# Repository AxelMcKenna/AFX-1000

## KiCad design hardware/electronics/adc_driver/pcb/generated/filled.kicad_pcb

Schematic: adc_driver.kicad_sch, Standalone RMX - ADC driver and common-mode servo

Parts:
C1, C2, C15, C16: 1pF C0G +/-0.1pF; C_0805_2012Metric
C3, C17: 47pF C0G 5%; C_0805_2012Metric
C4, C5, C18, C19: 22pF C0G 5%; C_0805_2012Metric
C6, C20: 100nF 25V X7R; C_0805_2012Metric
C7, C21: 1uF 63V film 10%; C_Rect_L7.2mm_W5.0mm_P5.00mm
C8, C22: 10uF 16V X7R; C_1206_3216Metric
C9, C23: 47uF 16V X7R; C_1210_3225Metric
C10, C11, C24, C25: 47uF 6.3V X7R; C_1206_3216Metric
C12, C26: 2.2uF 16V X7R; C_0805_2012Metric
C13, C14, C27, C28: 100nF 16V X7R; C_0805_2012Metric
C29, C30, C31, C32: 100nF 50V X7R; C_0805_2012Metric
C33, C34: 10uF 50V X7R; C_1210_3225Metric
D1, D2: BAT54S,215; SOT-23
J1: Conn_01x03; PinHeader_1x03_P2.54mm_Vertical
J2: Conn_01x07; PinHeader_1x07_P2.54mm_Vertical
J3, J4: Conn_01x04; PinHeader_1x04_P2.54mm_Vertical
R1, R2, R17, R18: 2.49k 0.1%; R_0805_2012Metric
R3, R4, R19, R20: 1.21k 0.1%; R_0805_2012Metric
R5, R6, R21, R22: 3.32R 0.1%; R_0805_2012Metric
R7, R23: 1M 1%; R_0805_2012Metric
R8, R9, R24, R25: 1M 0.1%; R_0805_2012Metric
R10, R11, R26, R27: 100k 0.1%; R_0805_2012Metric
R12, R28: 100M 1%; R_0805_2012Metric
R13, R29: 10k 1%; R_0805_2012Metric
R14, R30: 4.7k 1%; R_0805_2012Metric
R15, R31: 100k 1%; R_0805_2012Metric
R16, R32: 1R 1%; R_0805_2012Metric
R33: 1k 1%; R_0805_2012Metric
U1, U2: THS4551IDGKR; VSSOP-8_3x3mm_P0.65mm
U3: OPA1656ID; SOIC-8_3.9x4.9mm_P1.27mm
U4: OPA4192ID; SOIC-14_3.9x8.7mm_P1.27mm
U5, U6: LM7705MM/NOPB; VSSOP-8_3x3mm_P0.65mm

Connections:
/ADC_LN: C3.2, C5.1, J2.2, R3.1, R6.2, R11.1
/ADC_LP: C3.1, C4.1, J2.1, R4.1, R5.2, R10.1
/ADC_RN: C17.2, C19.1, J2.5, R19.1, R22.2, R27.1
/ADC_RP: C17.1, C18.1, J2.4, R20.1, R21.2, R26.1
/AGND: C4.2, C5.2, C6.2, C9.2, C10.2, C11.2, C12.2, C13.2, C14.2, C18.2, C19.2, C20.2, C23.2, C24.2, C25.2, C26.2, C27.2, C28.2, C29.2, C30.2, C31.2, C32.2, C33.2, C34.2, D1.1 (A1), D2.1 (A1), J1.2, J2.3, J3.2, J4.1, R2.1, R7.2, R9.2, R15.2, R18.1, R23.2, R25.2, R31.2, R33.2, U5.2 (VSS_A), U5.3 (SD), U5.5 (VSS_B), U6.2 (VSS_A), U6.3 (SD), U6.5 (VSS_B)
/BUF_L: R1.1, U3.1 (A_OUT), U3.2 (A-)
/BUF_R: R17.1, U3.6 (B-), U3.7 (B_OUT)
/CM_DRIVE_L: C7.1, R12.1, R13.1, U4.7 (B_OUT)
/CM_DRIVE_R: C21.1, R28.1, R29.1, U4.14 (D_OUT)
/CM_SENSE_L: C7.2, R10.2, R11.2, R12.2, U4.6 (B-)
/CM_SENSE_R: C21.2, R26.2, R27.2, R28.2, U4.13 (D-)
/DRV_ENABLE: J4.2, R14.1, R30.1
/DRV_LN: C1.1, R6.1, U1.5 (OUT-)
/DRV_LP: C2.1, R5.1, U1.4 (OUT+)
/DRV_RN: C15.1, R22.1, U2.5 (OUT-)
/DRV_RP: C16.1, R21.1, U2.4 (OUT+)
/FB_N_L: C2.2, R2.2, R4.2, U1.1 (IN-)
/FB_N_R: C16.2, R18.2, R20.2, U2.1 (IN-)
/FB_P_L: C1.2, R1.2, R3.2, U1.8 (IN+)
/FB_P_R: C15.2, R17.2, R19.2, U2.8 (IN+)
/FLY_N_L: C8.2, U5.8 (CF-)
/FLY_N_R: C22.2, U6.8 (CF-)
/FLY_P_L: C8.1, U5.1 (CF+)
/FLY_P_R: C22.1, U6.1 (CF+)
/N12: C30.1, C32.1, C34.1, J3.3, U3.4 (V-), U4.11 (V-)
/NBIAS_L: C11.1, C14.1, J4.3, R16.2, U1.6 (VS-)
/NBIAS_R: C25.1, C28.1, J4.4, R32.2, U2.6 (VS-)
/NPUMP_L: C10.1, R16.1, U5.6 (VOUT)
/NPUMP_R: C24.1, R32.1, U6.6 (VOUT)
/P12: C29.1, C31.1, C33.1, J3.1, U3.8 (V+), U4.4 (V+)
/PD_L: R14.2, R15.1, U1.7 (PD)
/PD_R: R30.2, R31.1, U2.7 (PD)
/PRE_OUT_L: J1.1, R7.1, U3.3 (A+)
/PRE_OUT_R: J1.3, R23.1, U3.5 (B+)
/REF_ADC1: J2.6, R8.1
/REF_ADC2: J2.7, R24.1
/REF_DIV_L: C6.1, R8.2, R9.1, U4.3 (A+)
/REF_DIV_R: C20.1, R24.2, R25.1, U4.10 (C+)
/REF_HALF_L: U4.1 (A_OUT), U4.2 (A-), U4.5 (B+)
/REF_HALF_R: U4.8 (C_OUT), U4.9 (C-), U4.12 (D+)
/RES_L: C9.1, U5.7 (CRES)
/RES_R: C23.1, U6.7 (CRES)
/V5_REG: C12.1, C13.1, C26.1, C27.1, D1.2 (K2), D2.2 (K2), J3.4, R33.1, U1.3 (VS+), U2.3 (VS+), U5.4 (VDD), U6.4 (VDD)
/VOCM_L: D1.3 (K1_A2), R13.2, U1.2 (VOCM)
/VOCM_R: D2.3 (K1_A2), R29.2, U2.2 (VOCM)

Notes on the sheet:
E12 ADC driver prototype: remote raw-pin gain feedback, separate reference-half servos, low-voltage output rails.
No PCB or bench validation. Actual converter loading, stability, full scale/noise, bias-rail windows and power faults require qualification.
THS4551 +/-outputs use V5_REG and per-channel LM7705 negative bias; no direct +/-12V output rail on raw ADC drivers.
Future PRE_ANALOG_OK must include V5_REG and BOTH filtered negative-bias windows. E09 CHIP_EN drives DRV_ENABLE.
U3 preserves E10 high input impedance. U4 buffers references/2 and slowly controls ADC-pin average; no unbuffered shared reference load.

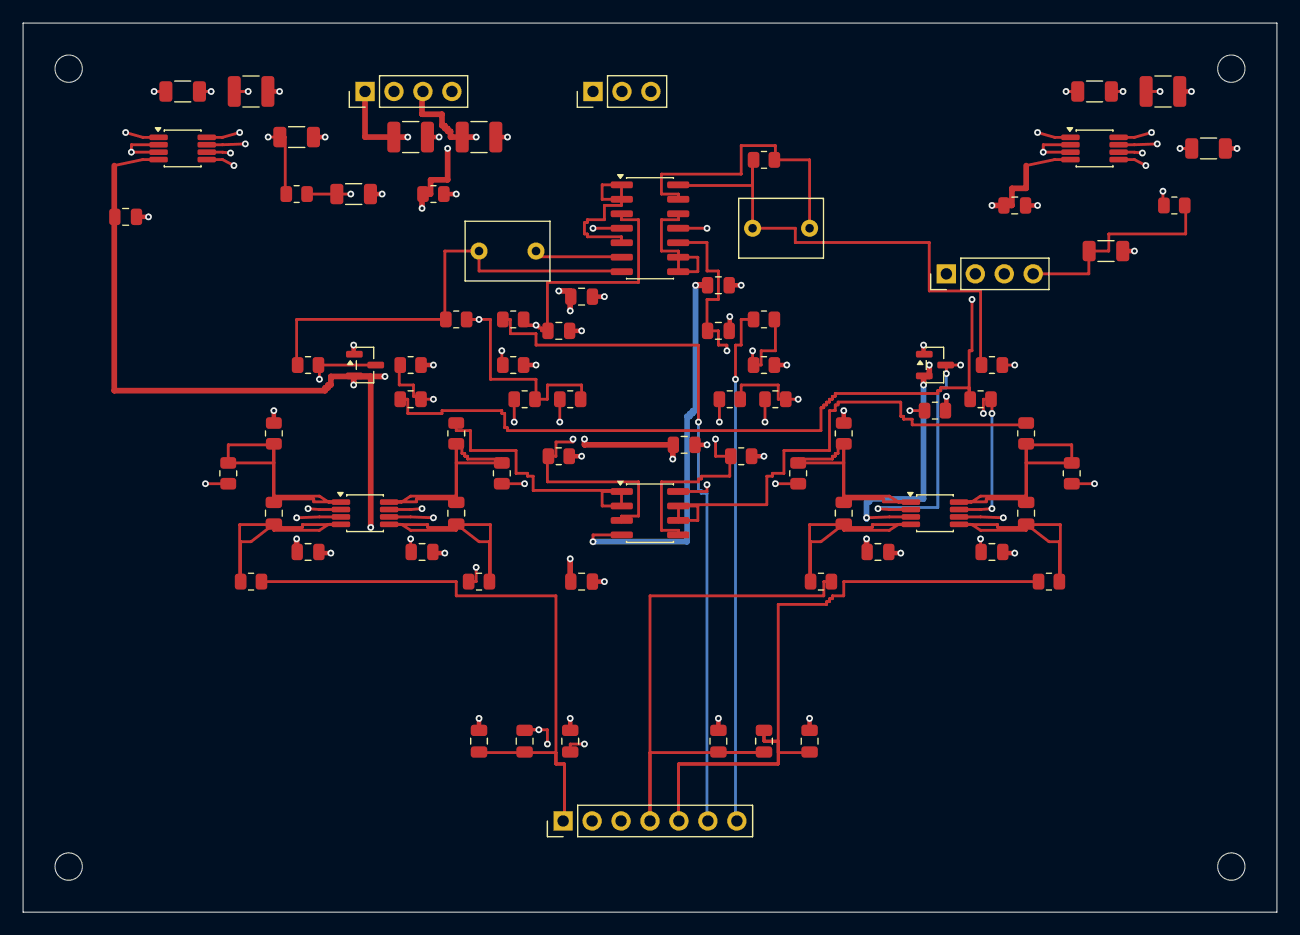
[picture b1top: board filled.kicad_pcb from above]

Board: 6 copper layers, 110.0 x 78.0 mm, 83 parts (0 on the bottom side), 45 nets.

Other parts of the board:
H1, H2, H3, H4: M2_CLEARANCE; M2_Clearance

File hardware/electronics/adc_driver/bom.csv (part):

Reference,Part_or_value,Footprint_candidate,Datasheet,Design_note
U1,THS4551IDGKR,Package_SO:VSSOP-8_3x3mm_P0.65mm,https://www.ti.com/lit/ds/symlink/ths4551.pdf,Remote raw-pin resistive feedback; local1pF high-frequency feedback. Low-voltage rails only.
U2,THS4551IDGKR,Package_SO:VSSOP-8_3x3mm_P0.65mm,https://www.ti.com/lit/ds/symlink/ths4551.pdf,Remote raw-pin resistive feedback; local1pF high-frequency feedback. Low-voltage rails only.
U3,OPA1656ID,Package_SO:SOIC-8_3.9x4.9mm_P1.27mm,https://www.ti.com/lit/ds/symlink/opa1656.pdf,High-impedance unity buffers preserve E10 load >=100k;1M returns per channel.
U4,OPA4192ID,Package_SO:SOIC-14_3.9x8.7mm_P1.27mm,https://www.ti.com/lit/ds/symlink/opa4192.pdf,A/C buffer separate reference halves;B/D slow average raw ADC pins to reference/2. No shared channel reference.
U5,LM7705MM/NOPB,Package_SO:VSSOP-8_3x3mm_P0.65mm,https://www.ti.com/lit/ds/symlink/lm7705.pdf,One bias generator/channel; output-current allocation <=20mA; effective pump capacitors must meet datasheet test values.
U6,LM7705MM/NOPB,Package_SO:VSSOP-8_3x3mm_P0.65mm,https://www.ti.com/lit/ds/symlink/lm7705.pdf,One bias generator/channel; output-current allocation <=20mA; effective pump capacitors must meet datasheet test values.
R1,2.49k 0.1%,Resistor_SMD:R_0805_2012Metric,,FDA source resistor; source buffer directly drives this resistive load
R2,2.49k 0.1%,Resistor_SMD:R_0805_2012Metric,,Matched ground leg
R3,1.21k 0.1%,Resistor_SMD:R_0805_2012Metric,,Remote negative-output feedback; gain reserves ADC clipping margin
R4,1.21k 0.1%,Resistor_SMD:R_0805_2012Metric,,Remote positive-output feedback
R5,3.32R 0.1%,Resistor_SMD:R_0805_2012Metric,,Raw-pin isolation; inside low-frequency feedback
R6,3.32R 0.1%,Resistor_SMD:R_0805_2012Metric,,Raw-pin isolation; inside low-frequency feedback
R7,1M 1%,Resistor_SMD:R_0805_2012Metric,,E10 load1M plus FET input; no direct low-resistance FDA load
R8,1M 0.1%,Resistor_SMD:R_0805_2012Metric,,High-impedance reference divider; load about1.65uA/channel
R9,1M 0.1%,Resistor_SMD:R_0805_2012Metric,,Reference half; hot input bias/offset allocation included in analysis
R10,100k 0.1%,Resistor_SMD:R_0805_2012Metric,,Common-mode average sense
R11,100k 0.1%,Resistor_SMD:R_0805_2012Metric,,Common-mode average sense
R12,100M 1%,Resistor_SMD:R_0805_2012Metric,,Finite dc servo gain; clean board/leakage qualification required
R13,10k 1%,Resistor_SMD:R_0805_2012Metric,,VOCM clamp current limit
R14,4.7k 1%,Resistor_SMD:R_0805_2012Metric,,3.3V CHIP_EN from E09; missing enable defaults off
R15,100k 1%,Resistor_SMD:R_0805_2012Metric,,PD pull-down
R16,1R 1%,Resistor_SMD:R_0805_2012Metric,,Bias-rail ripple filter; signed load drop included in headroom screen
C1,1pF C0G +/-0.1pF,Capacitor_SMD:C_0805_2012Metric,,Local high-frequency feedback; PCB parasitics and actual FDA loop need verification
C2,1pF C0G +/-0.1pF,Capacitor_SMD:C_0805_2012Metric,,Local high-frequency feedback
C3,47pF C0G 5%,Capacitor_SMD:C_0805_2012Metric,,"Differential RF capacitor, not a proven switched-capacitor kickback model"
C4,22pF C0G 5%,Capacitor_SMD:C_0805_2012Metric,,Raw-pin RF common-mode cap
C5,22pF C0G 5%,Capacitor_SMD:C_0805_2012Metric,,Raw-pin RF common-mode cap
C6,100nF 25V X7R,Capacitor_SMD:C_0805_2012Metric,,Effective50..150nF allocation; reference-half filter
C7,1uF 63V film 10%,Capacitor_THT:C_Rect_L7.2mm_W5.0mm_P5.00mm,,"WIMA MKS2C041001F00KSSD; servo effective0.9..1.1uF, leakage qualification required"
C8,10uF 16V X7R,Capacitor_SMD:C_1206_3216Metric,,Require effective >=5uF at actual flying-cap bias
C9,47uF 16V X7R,Capacitor_SMD:C_1210_3225Metric,,Require effective >=22uF at about5V negative reserve bias
C10,47uF 6.3V X7R,Capacitor_SMD:C_1206_3216Metric,,Require effective >=22uF; native LM7705 output capacitor
C11,47uF 6.3V X7R,Capacitor_SMD:C_1206_3216Metric,,Require effective >=22uF; post1Ohm bias filter
C12,2.2uF 16V X7R,Capacitor_SMD:C_0805_2012Metric,,Local pump input; require effective >=1uF
C13,100nF 16V X7R,Capacitor_SMD:C_0805_2012Metric,,Local FDA positive bypass
C14,100nF 16V X7R,Capacitor_SMD:C_0805_2012Metric,,Local FDA negative bypass
D1,"BAT54S,215",Package_TO_SOT_SMD:SOT-23,https://assets.nexperia.com/documents/data-sheet/BAT54S.pdf,Series Schottky pair clamps VOCM; not a raw ADC signal shunt.
R17,2.49k 0.1%,Resistor_SMD:R_0805_2012Metric,,FDA source resistor; source buffer directly drives this resistive load
R18,2.49k 0.1%,Resistor_SMD:R_0805_2012Metric,,Matched ground leg
R19,1.21k 0.1%,Resistor_SMD:R_0805_2012Metric,,Remote negative-output feedback; gain reserves ADC clipping margin
R20,1.21k 0.1%,Resistor_SMD:R_0805_2012Metric,,Remote positive-output feedback
R21,3.32R 0.1%,Resistor_SMD:R_0805_2012Metric,,Raw-pin isolation; inside low-frequency feedback
R22,3.32R 0.1%,Resistor_SMD:R_0805_2012Metric,,Raw-pin isolation; inside low-frequency feedback
R23,1M 1%,Resistor_SMD:R_0805_2012Metric,,E10 load1M plus FET input; no direct low-resistance FDA load
R24,1M 0.1%,Resistor_SMD:R_0805_2012Metric,,High-impedance reference divider; load about1.65uA/channel
R25,1M 0.1%,Resistor_SMD:R_0805_2012Metric,,Reference half; hot input bias/offset allocation included in analysis
R26,100k 0.1%,Resistor_SMD:R_0805_2012Metric,,Common-mode average sense
R27,100k 0.1%,Resistor_SMD:R_0805_2012Metric,,Common-mode average sense
R28,100M 1%,Resistor_SMD:R_0805_2012Metric,,Finite dc servo gain; clean board/leakage qualification required
R29,10k 1%,Resistor_SMD:R_0805_2012Metric,,VOCM clamp current limit
R30,4.7k 1%,Resistor_SMD:R_0805_2012Metric,,3.3V CHIP_EN from E09; missing enable defaults off
R31,100k 1%,Resistor_SMD:R_0805_2012Metric,,PD pull-down
R32,1R 1%,Resistor_SMD:R_0805_2012Metric,,Bias-rail ripple filter; signed load drop included in headroom screen
C15,1pF C0G +/-0.1pF,Capacitor_SMD:C_0805_2012Metric,,Local high-frequency feedback; PCB parasitics and actual FDA loop need verification
C16,1pF C0G +/-0.1pF,Capacitor_SMD:C_0805_2012Metric,,Local high-frequency feedback
C17,47pF C0G 5%,Capacitor_SMD:C_0805_2012Metric,,"Differential RF capacitor, not a proven switched-capacitor kickback model"
C18,22pF C0G 5%,Capacitor_SMD:C_0805_2012Metric,,Raw-pin RF common-mode cap
C19,22pF C0G 5%,Capacitor_SMD:C_0805_2012Metric,,Raw-pin RF common-mode cap
C20,100nF 25V X7R,Capacitor_SMD:C_0805_2012Metric,,Effective50..150nF allocation; reference-half filter
C21,1uF 63V film 10%,Capacitor_THT:C_Rect_L7.2mm_W5.0mm_P5.00mm,,"WIMA MKS2C041001F00KSSD; servo effective0.9..1.1uF, leakage qualification required"
C22,10uF 16V X7R,Capacitor_SMD:C_1206_3216Metric,,Require effective >=5uF at actual flying-cap bias
C23,47uF 16V X7R,Capacitor_SMD:C_1210_3225Metric,,Require effective >=22uF at about5V negative reserve bias
C24,47uF 6.3V X7R,Capacitor_SMD:C_1206_3216Metric,,Require effective >=22uF; native LM7705 output capacitor
C25,47uF 6.3V X7R,Capacitor_SMD:C_1206_3216Metric,,Require effective >=22uF; post1Ohm bias filter
C26,2.2uF 16V X7R,Capacitor_SMD:C_0805_2012Metric,,Local pump input; require effective >=1uF
C27,100nF 16V X7R,Capacitor_SMD:C_0805_2012Metric,,Local FDA positive bypass
C28,100nF 16V X7R,Capacitor_SMD:C_0805_2012Metric,,Local FDA negative bypass
D2,"BAT54S,215",Package_TO_SOT_SMD:SOT-23,https://assets.nexperia.com/documents/data-sheet/BAT54S.pdf,Series Schottky pair clamps VOCM; not a raw ADC signal shunt.
R33,1k 1%,Resistor_SMD:R_0805_2012Metric,,5V bleeder; does not establish zero back-power or arbitrary fault protection
C29,100nF 50V X7R,Capacitor_SMD:C_0805_2012Metric,,U3 local positive
C30,100nF 50V X7R,Capacitor_SMD:C_0805_2012Metric,,U3 local negative
C31,100nF 50V X7R,Capacitor_SMD:C_0805_2012Metric,,U4 local positive
C32,100nF 50V X7R,Capacitor_SMD:C_0805_2012Metric,,U4 local negative
C33,10uF 50V X7R,Capacitor_SMD:C_1210_3225Metric,,Require effective >=4.7uF; exact MPN unselected
C34,10uF 50V X7R,Capacitor_SMD:C_1210_3225Metric,,Require effective >=4.7uF; exact MPN unselected
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
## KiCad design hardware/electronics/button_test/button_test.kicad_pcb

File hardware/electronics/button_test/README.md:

# B01 button test PCB

This is a passive **32 × 16 × 1.6 mm test board** for the
[guided button fit fixture](../../cad/BUTTON-FIT.md): one B3F-1000, two M2 holes
22 mm apart, and a two-wire/2.54 mm connector. It is not the full control PCB
and contains no audio or power circuitry.

Open [button_test.kicad_pro](button_test.kicad_pro) in KiCad. The schematic,
board, passive symbols and three footprints are local. Switch holes follow the
manufacturer's top-view 6.5 × 4.5 mm pattern with 1 mm drills. No original RMX PCB
was copied.

| Terminal | Connect |
| --- | --- |
| J1 pin 1, S | Logic input with 3.3 V pull-up, or continuity lead |
| J1 pin 2, G | Ground, or other continuity lead |

Upper switch pads 3/4 are Signal; lower pads 1/2 are Ground in the manufacturer's
top view. Confirm against the actual part before soldering. Pressing joins the
two rows. Do not wire these terminals directly across a power supply.

The [native record](generated/verification.json) captures KiCad ERC, all-severity
DRC, unconnected-pad check, schematic parity and exported pin nets. All have zero
issues at the recorded hashes. **Physical fit, assembly and button operation
remain untested.** These checks apply only to this small passive board.

Native exports: [top](generated/board-top.svg), [bottom](generated/board-bottom.svg),
[schematic](generated/button_test.svg). The
[drill template](../../cad/generated/button-pcb-drill.svg) includes a 32 mm scale
check; print at 100%. It is a prototype aid without drill compensation.

    python3 -m hardware.electronics.button_test.generate
    python3 -m hardware.electronics.button_test.verify --kicad-cli /path/to/kicad-cli

KiCad 10.0.7 was checked from the official read-only application image with an
isolated configuration. The verifier stops on any ERC/DRC violation and confirms
the exported nets contain exactly J1.1/SW1.3/SW1.4 and J1.2/SW1.1/SW1.2.

Generation replaces the generated board/schematic; make persistent edits in
the generator, or stop regenerating when continuing directly in KiCad.
No board has been ordered, fabricated or released for production.

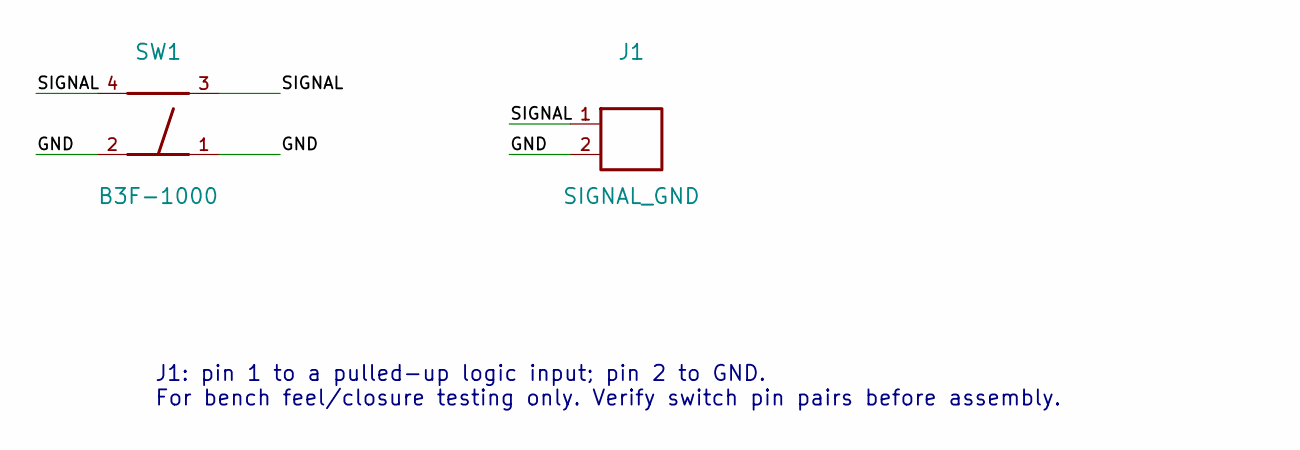
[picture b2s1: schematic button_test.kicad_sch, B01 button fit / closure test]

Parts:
J1: SIGNAL_GND; WirePair254
SW1: B3F-1000; B3F1000

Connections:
/GND: J1.2, SW1.1, SW1.2
/SIGNAL: J1.1, SW1.3, SW1.4

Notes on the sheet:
J1: pin 1 to a pulled-up logic input; pin 2 to GND. For bench feel/closure testing only. Verify switch pin pairs before assembly.

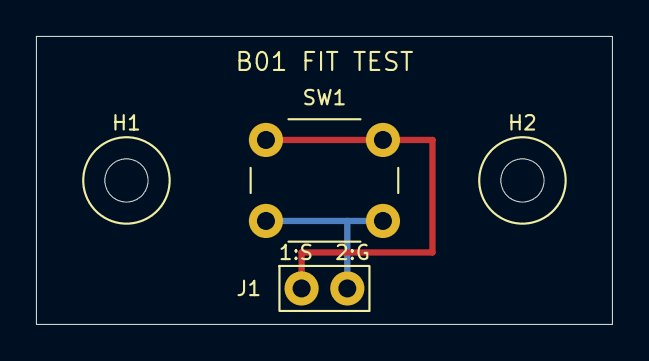
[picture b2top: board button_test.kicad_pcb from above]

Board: 2 copper layers, 32.0 x 16.0 mm, 4 parts (0 on the bottom side), 2 nets.

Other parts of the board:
H1, H2: M2; M2_Clearance
